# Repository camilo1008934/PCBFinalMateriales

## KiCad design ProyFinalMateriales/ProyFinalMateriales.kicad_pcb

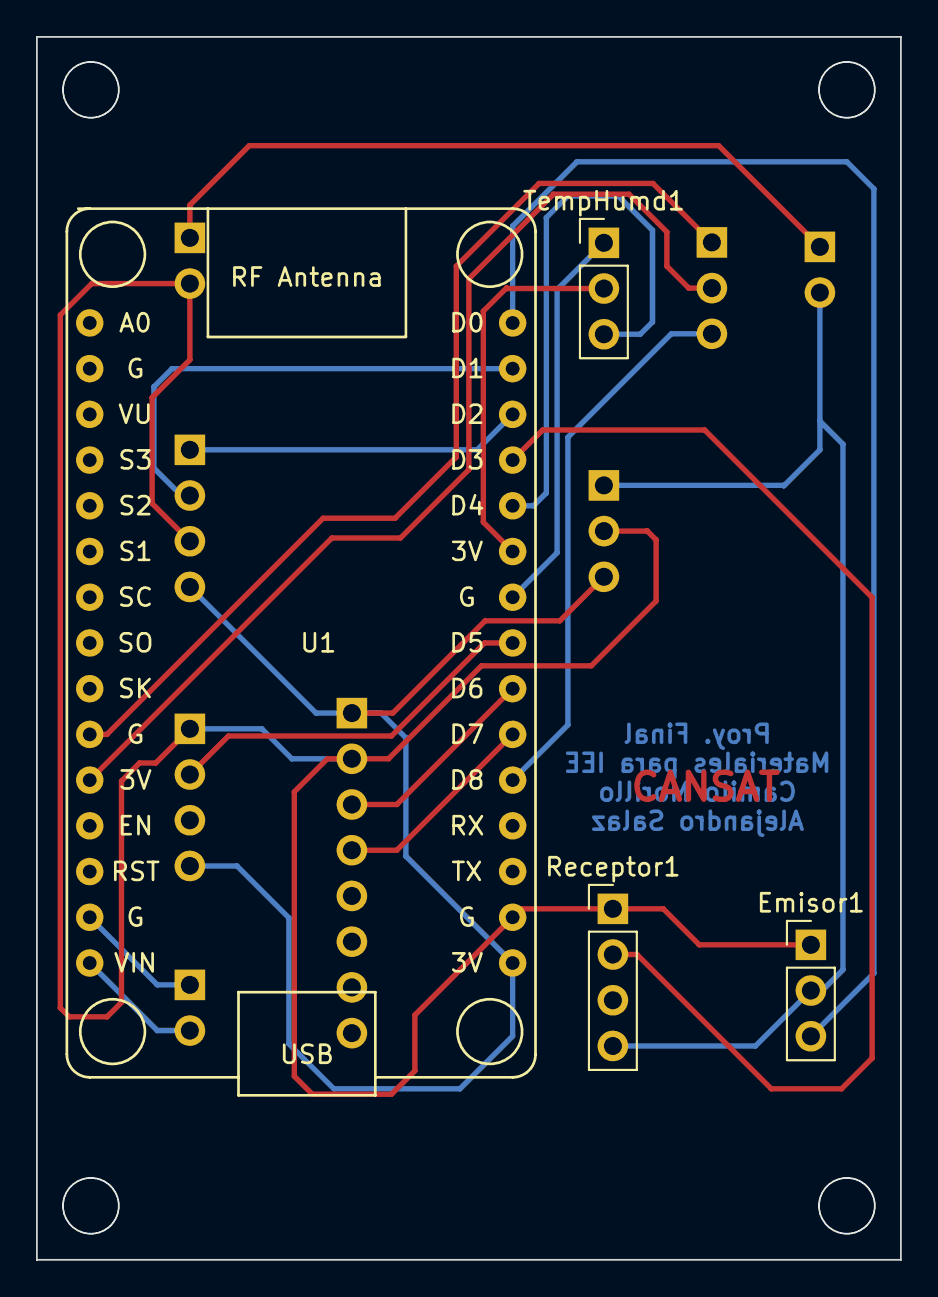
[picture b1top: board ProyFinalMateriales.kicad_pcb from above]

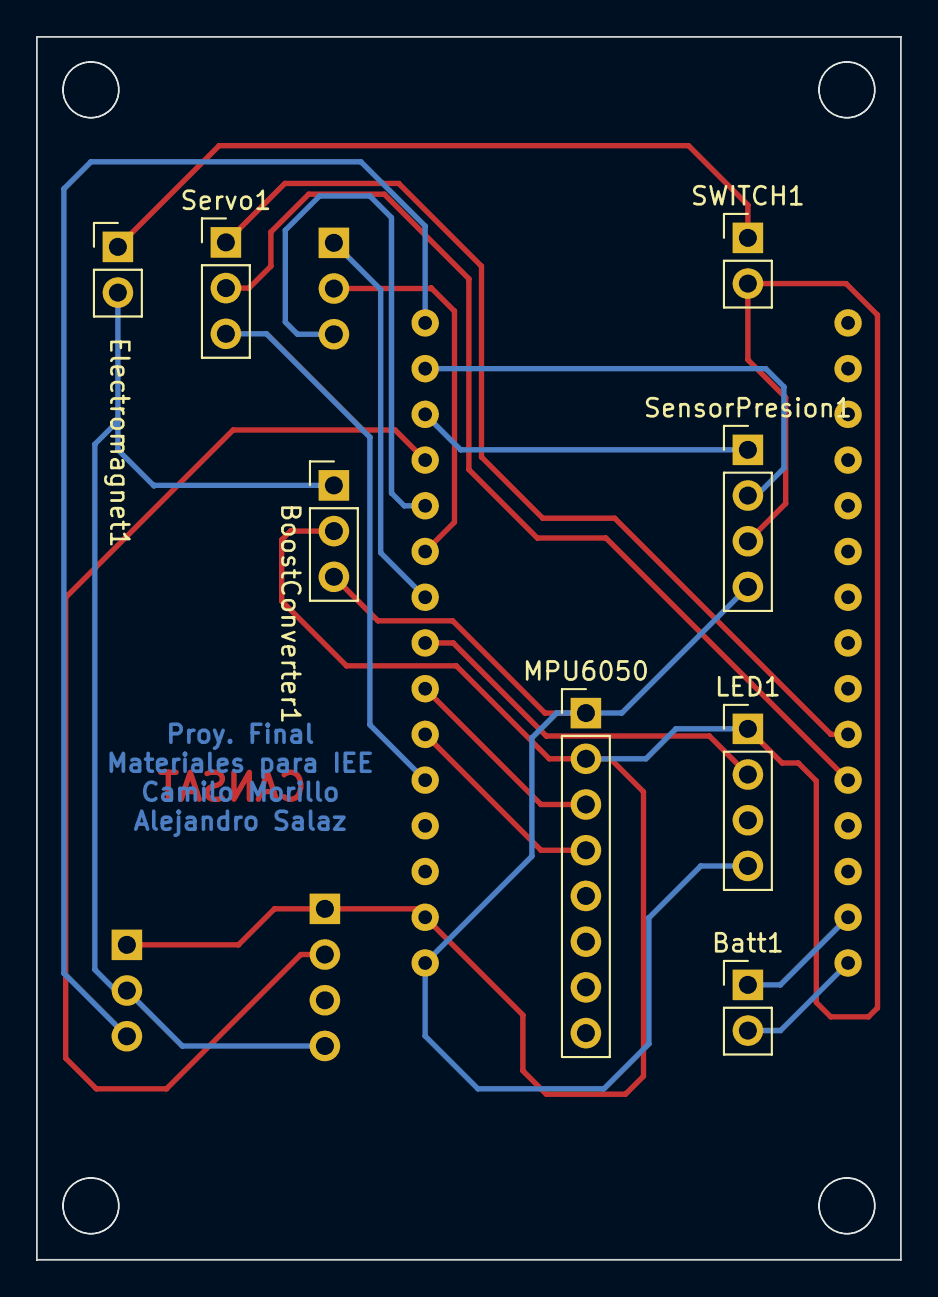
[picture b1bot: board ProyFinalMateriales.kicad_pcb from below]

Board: 2 copper layers, 48.0 x 67.9 mm, 12 parts (8 on the bottom side), 19 nets.

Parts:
Batt1: Conn_01x02_Male; PinHeader_1x02_P2.54mm_Vertical
BoostConverter1: Conn_01x03_Male; PinHeader_1x03_P2.54mm_Vertical
Electromagnet1: Conn_01x02_Male; PinHeader_1x02_P2.54mm_Vertical
Emisor1: Conn_01x03_Male; PinHeader_1x03_P2.54mm_Vertical
LED1: Conn_01x04_Male; PinHeader_1x04_P2.54mm_Vertical
MPU6050: Conn_01x08_Male; PinHeader_1x08_P2.54mm_Vertical
Receptor1: Conn_01x04_Male; PinHeader_1x04_P2.54mm_Vertical
SWITCH1: Conn_01x02_Male; PinHeader_1x02_P2.54mm_Vertical
SensorPresion1: Conn_01x04_Male; PinHeader_1x04_P2.54mm_Vertical
Servo1: Conn_01x03_Male; PinHeader_1x03_P2.54mm_Vertical
TempHumd1: Conn_01x03_Male; PinHeader_1x03_P2.54mm_Vertical
U1: NodeMCU1.0(ESP-12E); ESP12F-Devkit-V3

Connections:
3.3V1: BoostConverter1.3, LED1.4, MPU6050.1, SensorPresion1.4, U1.16 (3.3V)
3.3V2: Servo1.2, U1.11 (3.3V)
3.3V3: TempHumd1.2, U1.25 (3.3V)
5V: BoostConverter1.1, Electromagnet1.2, Emisor1.2, Receptor1.4
GND1: BoostConverter1.2, Emisor1.1, LED1.1, MPU6050.2, Receptor1.1, SWITCH1.2, SensorPresion1.3, U1.17 (GND)
GND2: Servo1.1, U1.10 (GND)
GND3: TempHumd1.1, U1.24 (GND)
GNDEM: Electromagnet1.1, SWITCH1.1
GPIO0: Receptor1.2, U1.27 (D3(GPIO0))
GPIO2: TempHumd1.3, U1.26 (D4(GPIO2))
GPIO4: SensorPresion1.1, U1.28 (D2(GPIO4))
GPIO5: SensorPresion1.2, U1.29 (D1(GPIO5))
GPIO12: MPU6050.3, U1.22 (D6(GPIO12))
GPIO13: MPU6050.4, U1.21 (D7(GPIO13))
GPIO14: LED1.2, U1.23 (D5(GPIO14))
GPIO15: Servo1.3, U1.20 (D8(GPIO15))
GPIO16: Emisor1.3, U1.30 (D0(GPIO16))
unnamed: Batt1.1, U1.14 (GND)
unnamed: Batt1.2, U1.15 (VIN)

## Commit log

2022-11-17 first commit;
